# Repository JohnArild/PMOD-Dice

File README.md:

# PMOD-Dice
Small board with LEDs in a Dice pattern with PMOD interface

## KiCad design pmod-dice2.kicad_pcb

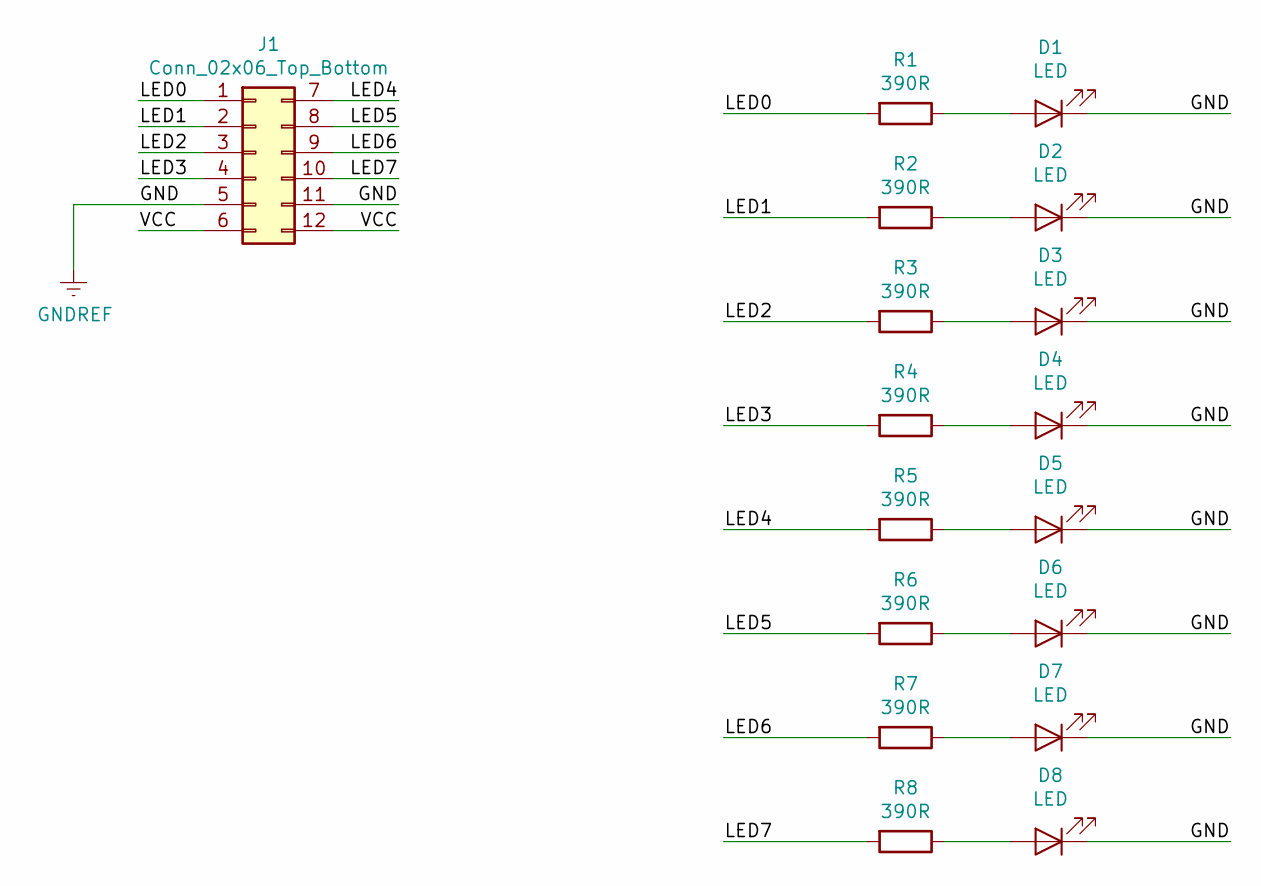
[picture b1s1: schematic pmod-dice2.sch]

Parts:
D1, D2, D3, D4, D5, D6, D7, D8: LED; LED_0603_1608Metric
J1: Conn_02x06_Top_Bottom; PinHeader_2x06
R1, R2, R3, R4, R5, R6, R7, R8: 390R; R_0603_1608Metric

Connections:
/LED0: J1.1, R1.2
/LED1: J1.2, R2.2
/LED2: J1.3, R3.2
/LED3: J1.4, R4.2
/LED4: J1.7, R5.2
/LED5: J1.8, R6.2
/LED6: J1.9, R7.2
/LED7: J1.10, R8.2
/VCC: J1.6, J1.12
GNDREF: D1.1 (K), D2.1 (K), D3.1 (K), D4.1 (K), D5.1 (K), D6.1 (K), D7.1 (K), D8.1 (K), J1.5, J1.11
unnamed: D1.2 (A), R1.1
unnamed: D2.2 (A), R2.1
unnamed: D3.2 (A), R3.1
unnamed: D4.2 (A), R4.1
unnamed: D5.2 (A), R5.1
unnamed: D6.2 (A), R6.1
unnamed: D7.2 (A), R7.1
unnamed: D8.2 (A), R8.1

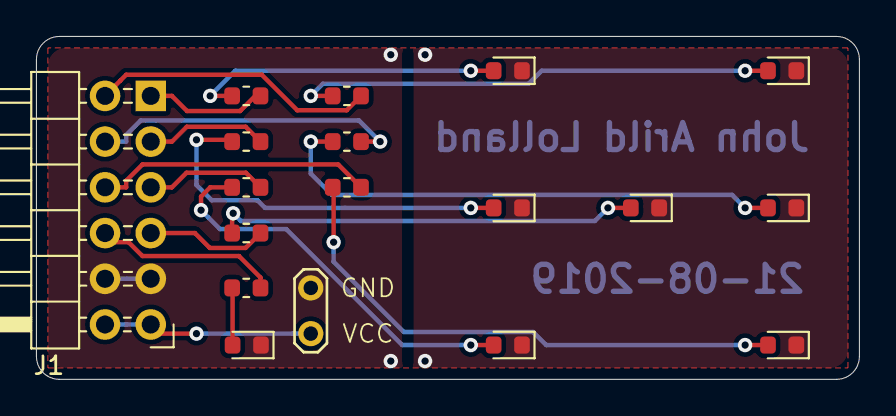
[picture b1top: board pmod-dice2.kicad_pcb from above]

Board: 2 copper layers, 45.7 x 19.1 mm, 17 parts (0 on the bottom side), 18 nets.

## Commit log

2019-09-09 Vivado project
